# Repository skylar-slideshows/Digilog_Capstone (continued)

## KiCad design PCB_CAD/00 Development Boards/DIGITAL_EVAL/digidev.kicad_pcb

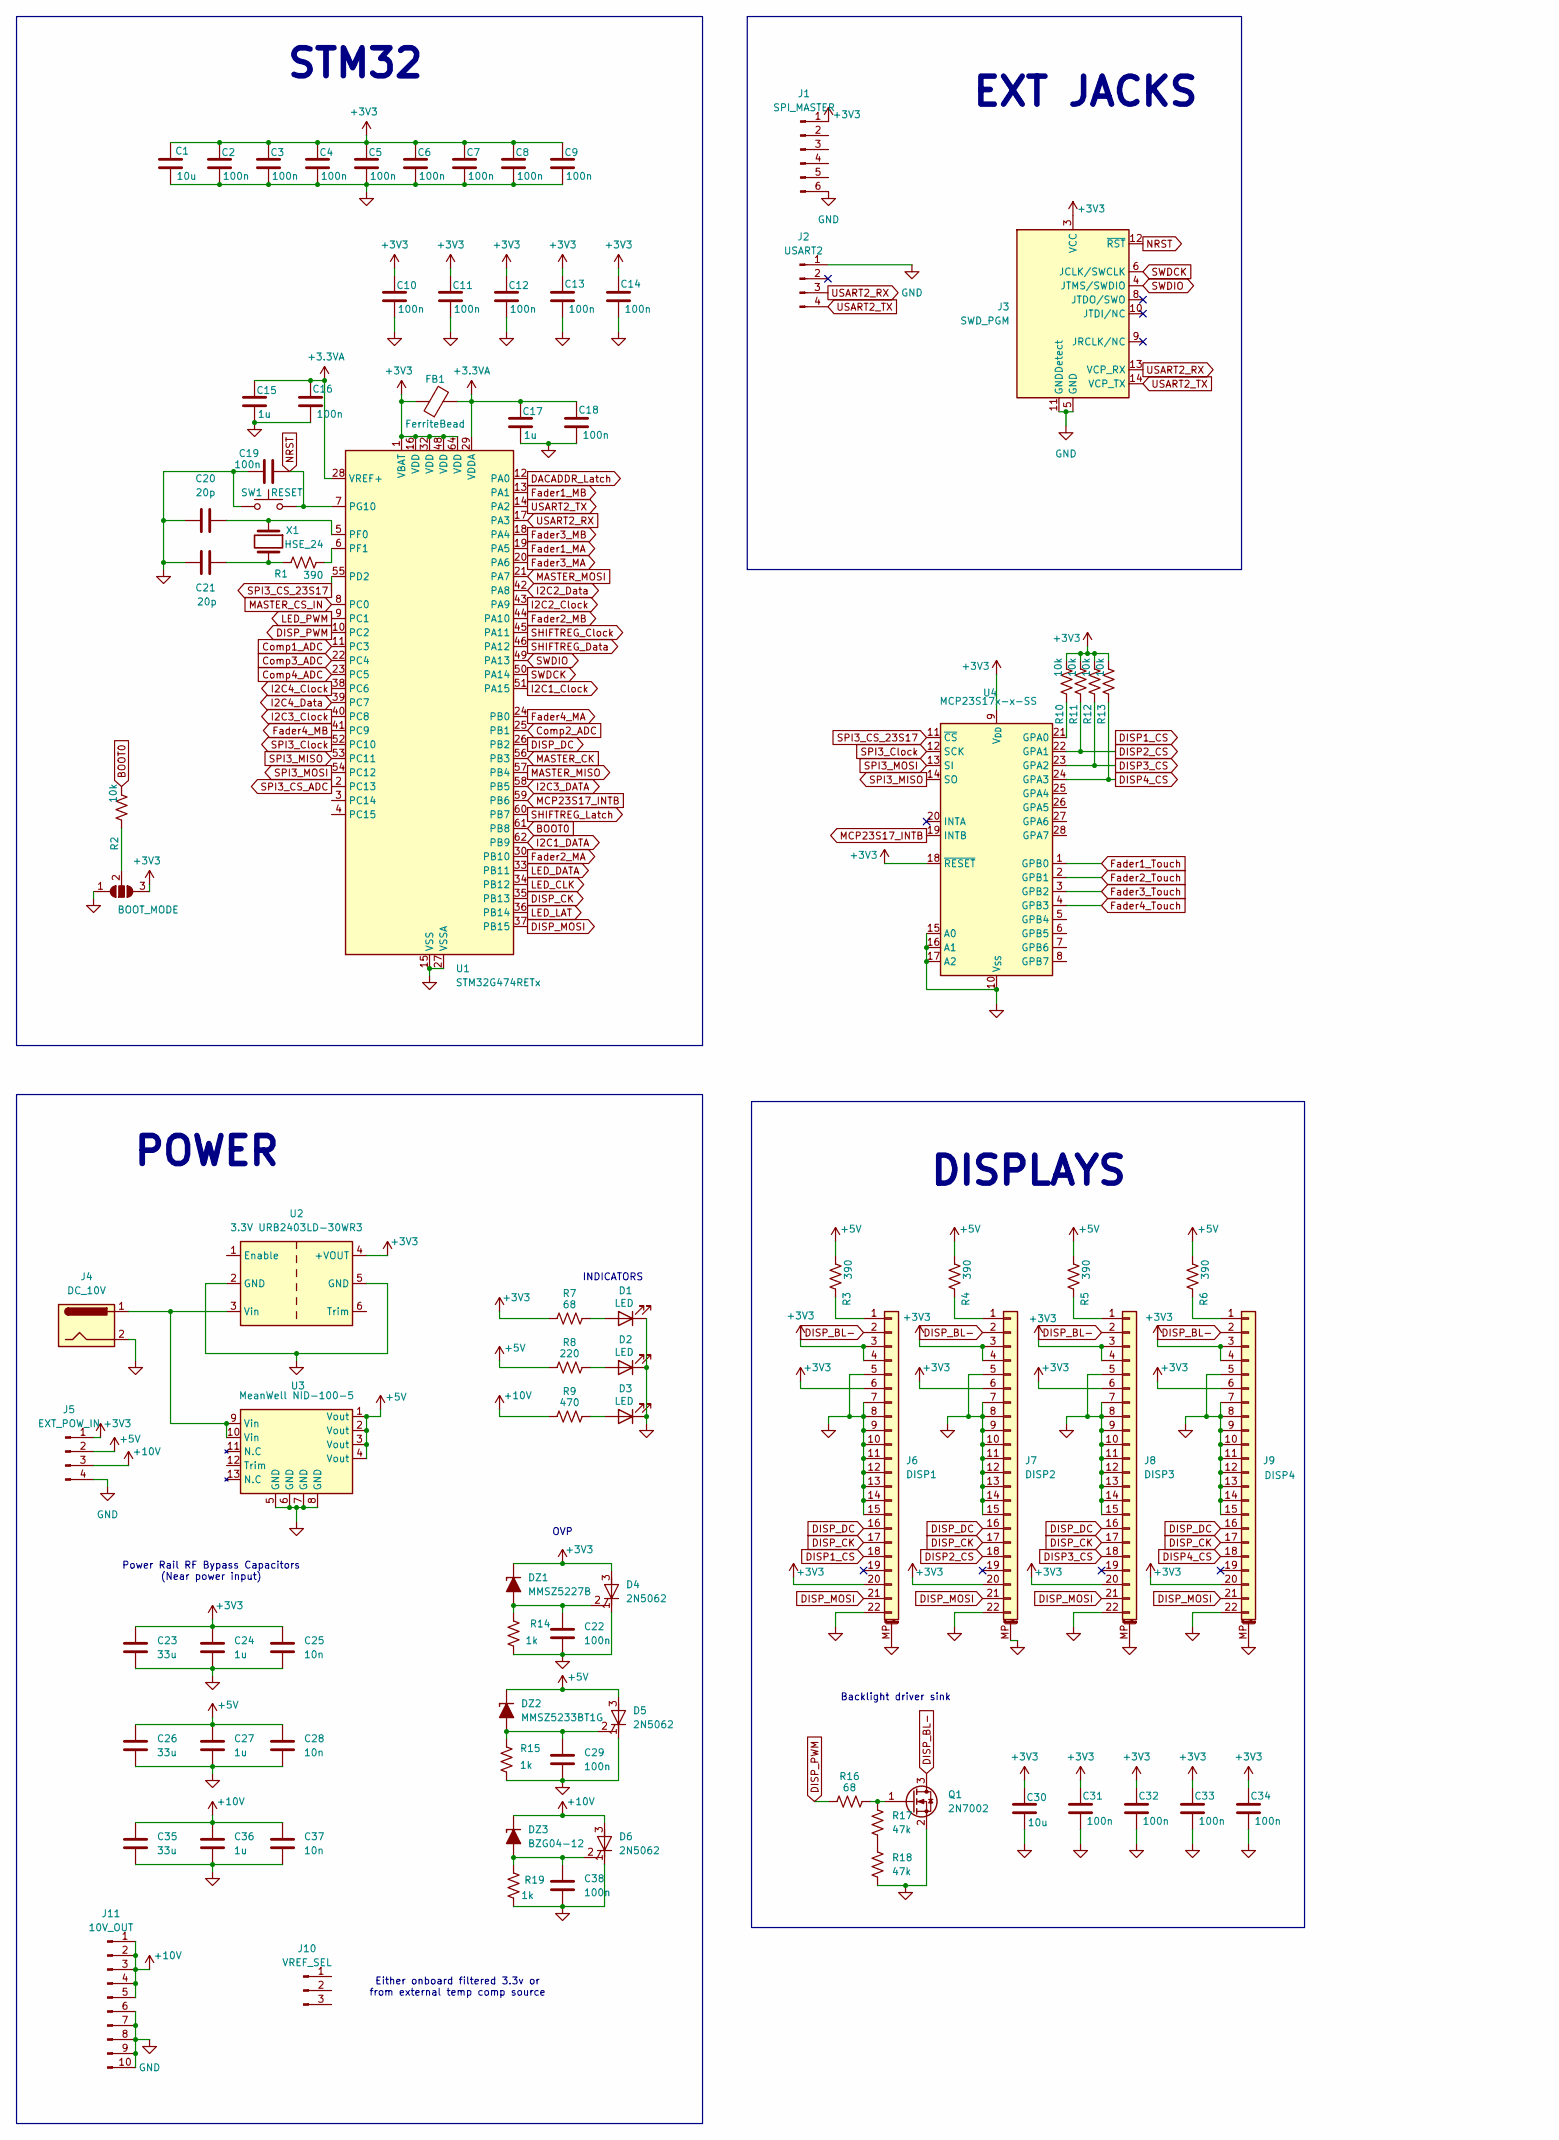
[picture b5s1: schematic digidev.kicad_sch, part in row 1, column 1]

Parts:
BOOT_MODE: SolderJumper_3_Open; SolderJumper-3_P2.0mm_Open_TrianglePad1.0x1.5mm
C1, C30: 10u; C_0805_2012Metric; LCSC C1713
C2, C3, C4, C5, C6, C7, C8, C9, C10, C11, C12, C13, C14, C16, C18, C19, C22, C29, C31, C32, C33, C34, C38: 100n; C_0603_1608Metric; LCSC C57112
C15, C17: 1u; C_0603_1608Metric; LCSC C57112
C20, C21: 20p; C_0603_1608Metric; LCSC C1648
C23, C26, C35: 33u; CP_Elec_6.3x5.4; LCSC C970684
C24, C27, C36: 1u; C_0603_1608Metric; LCSC C15849
C25, C28, C37: 10n; C_0603_1608Metric; LCSC C57112
D1, D2, D3: LED; LED_Rectangular_W3.9mm_H1.8mm
D4, D5, D6: 2N5062; TO-92
DZ1: MMSZ5227B; D_SOD-123; LCSC C707159
DZ2: MMSZ5233BT1G; D_SOD-123; LCSC C145506
DZ3: BZG04-12; D_DO-214AC_SMA; LCSC C5185905
FB1: FerriteBead; Ferrite_0603_1608Metric; LCSC C1002
J1: SPI_MASTER; PinHeader_1x06_P2.54mm_Vertical
J2: USART2; PinHeader_1x04_P2.54mm_Vertical
J3: SWD_PGM; FTSH-107-01-L-DV-K-TR; LCSC C5307809
J4: DC_10V; BarrelJack_Horizontal
J5: EXT_POW_IN; PinHeader_1x04_P2.54mm_Vertical
J6: DISP1; TE_2-1734839-2_1x22-1MP_P0.5mm_Horizontal; LCSC C22435644
J7: DISP2; TE_2-1734839-2_1x22-1MP_P0.5mm_Horizontal; LCSC C22435644
J8: DISP3; TE_2-1734839-2_1x22-1MP_P0.5mm_Horizontal; LCSC C22435644
J9: DISP4; TE_2-1734839-2_1x22-1MP_P0.5mm_Horizontal; LCSC C22435644
J10: VREF_SEL; PinHeader_1x03_P2.54mm_Vertical
J11: 10V_OUT; PinHeader_1x10_P2.54mm_Vertical
Q1: 2N7002; SOT-23; LCSC C85047
R1, R3, R4, R5, R6: 390; R_1206_3216Metric; LCSC C497314
R2, R10, R11, R12, R13: 10k; R_0603_1608Metric; LCSC C25804
R7, R16: 68; R_1206_3216Metric; LCSC C294793
R8: 220; R_1206_3216Metric; LCSC C25363
R9: 470; R_1206_3216Metric; LCSC C25383
R14, R15, R19: 1k; R_0603_1608Metric; LCSC C21190
R17, R18: 47k; R_0603_1608Metric; LCSC C25819
SW1: RESET; SW_Push_1P1T_NO_CK_KMR2; LCSC C72443
U1: STM32G474RETx; LQFP-64_10x10mm_P0.5mm; LCSC C521608
U2: 3.3V URB2403LD-30WR3; urb 50w dc-dc
U3: MeanWell NID-100-5; MeanWell NID100
U4: MCP23S17x-x-SS; SSOP-28_5.3x10.2mm_P0.65mm; LCSC C148009
X1: HSE_24; Crystal_SMD_HC49-SD; LCSC C117881

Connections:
+3.3VA: C15.1, C16.1, C17.1, C18.1, FB1.2, U1.28 (VREF+), U1.29 (VDDA); also elsewhere on the board
+3V3: BOOT_MODE.3 (B), C1.1, C2.1, C3.1, C4.1, C5.1, C6.1, C7.1, C8.1, C9.1, C10.1, C11.1, C12.1, C13.1, C14.1, C23.1, C24.1, C25.1, C30.1, C31.1, C32.1, C33.1, C34.1, D4.3 (A), DZ1.1 (K), FB1.1, J1.1, J3.3 (VCC), J5.1, J6.3, J6.4, J6.6, J6.20, J7.3, J7.4, J7.6, J7.20, J8.3, J8.4, J8.6, J8.20, J9.3, J9.4, J9.6, J9.20, R7.1, R10.1, R11.1, R12.1, R13.1, U1.1 (VBAT), U1.16 (VDD), U1.32 (VDD), U1.48 (VDD), U1.64 (VDD), U2.4 (+VOUT), U4.9 (V_{DD}), U4.18 (~RESET); also elsewhere on the board
+5V: C26.1, C27.1, C28.1, D5.3 (A), DZ2.1 (K), J5.2, R3.2, R4.2, R5.2, R6.2, R8.1, U3.1 (Vout), U3.2 (Vout), U3.3 (Vout), U3.4 (Vout)
+10V: C35.1, C36.1, C37.1, D6.3 (A), DZ3.1 (K), J5.3, J11.1, J11.2, J11.3, J11.4, J11.5, R9.1
BOOT0: R2.1, U1.61 (PB8)
Comp1_ADC: U1.11 (PC3)
Comp2_ADC: U1.25 (PB1)
Comp3_ADC: U1.22 (PC4)
Comp4_ADC: U1.23 (PC5)
DACADDR_Latch: U1.12 (PA0); also elsewhere on the board
DISP_BL-: J6.2, J7.2, J8.2, J9.2, Q1.3 (D)
DISP_CK: J6.17, J7.17, J8.17, J9.17, U1.35 (PB13)
DISP_DC: J6.16, J7.16, J8.16, J9.16, U1.26 (PB2)
DISP_MOSI: J6.21, J7.21, J8.21, J9.21, U1.37 (PB15)
DISP_PWM: R16.1, U1.10 (PC2)
Fader1_MA: U1.19 (PA5)
Fader1_MB: U1.13 (PA1)
Fader1_Touch: U4.1 (GPB0)
Fader2_MA: U1.30 (PB10)
Fader2_MB: U1.44 (PA10)
Fader2_Touch: U4.2 (GPB1)
Fader3_MA: U1.20 (PA6)
Fader3_MB: U1.18 (PA4)
Fader3_Touch: U4.3 (GPB2)
Fader4_MA: U1.24 (PB0)
Fader4_MB: U1.41 (PC9)
Fader4_Touch: U4.4 (GPB3)
GND: BOOT_MODE.1 (A), C1.2, C2.2, C3.2, C4.2, C5.2, C6.2, C7.2, C8.2, C9.2, C10.2, C11.2, C12.2, C13.2, C14.2, C15.2, C16.2, C17.2, C18.2, C19.1, C20.2, C21.1, C22.2, C23.2, C24.2, C25.2, C26.2, C27.2, C28.2, C29.2, C30.2, C31.2, C32.2, C33.2, C34.2, C35.2, C36.2, C37.2, C38.2, D1.1 (K), D2.1 (K), D3.1 (K), D4.1 (K), D5.1 (K), D6.1 (K), J1.6, J2.1, J3.5 (GND), J3.7 (GND), J3.11 (GNDDetect), J4.2, J5.4, J6.5, J6.7, J6.8, J6.9, J6.10, J6.11, J6.12, J6.13, J6.14, J6.15, J6.22, J6.MP (MountPin), J7.5, J7.7, J7.8, J7.9, J7.10, J7.11, J7.12, J7.13, J7.14, J7.15, J7.22, J7.MP (MountPin), J8.5, J8.7, J8.8, J8.9, J8.10, J8.11, J8.12, J8.13, J8.14, J8.15, J8.22, J8.MP (MountPin), J9.5, J9.7, J9.8, J9.9, J9.10, J9.11, J9.12, J9.13, J9.14, J9.15, J9.22, J9.MP (MountPin), J11.6, J11.7, J11.8, J11.9, J11.10, Q1.2 (S), R14.1, R15.1, R18.2, R19.2, SW1.1, U1.15 (VSS), U1.27 (VSSA), U1.31 (VSS), U1.47 (VSS), U1.63 (VSS), U2.2 (GND), U2.5 (GND), U3.5 (GND), U3.6 (GND), U3.7 (GND), U3.8 (GND), U4.10 (V_{SS}), U4.15 (A0), U4.16 (A1), U4.17 (A2); also elsewhere on the board
I2C1_Clock: U1.51 (PA15); also elsewhere on the board
I2C1_DATA: U1.62 (PB9); also elsewhere on the board
I2C2_Clock: U1.43 (PA9); also elsewhere on the board
I2C2_Data: U1.42 (PA8); also elsewhere on the board
I2C3_Clock: U1.40 (PC8); also elsewhere on the board
I2C3_DATA: U1.58 (PB5); also elsewhere on the board
I2C4_Clock: U1.38 (PC6); also elsewhere on the board
I2C4_Data: U1.39 (PC7); also elsewhere on the board
LED_CLK: U1.34 (PB12)
LED_DATA: U1.33 (PB11)
LED_LAT: U1.36 (PB14)
LED_PWM: U1.9 (PC1)
MASTER_CK: U1.56 (PB3)
MASTER_CS_IN: U1.8 (PC0)
MASTER_MISO: U1.57 (PB4)
MASTER_MOSI: U1.21 (PA7)
MCP23S17_INTB: U1.59 (PB6), U4.19 (INTB)
NRST: C19.2, J3.12 (~RST), SW1.2, U1.7 (PG10)
unnamed 66: BOOT_MODE.2 (C), R2.2; also elsewhere on the board
unnamed: C21.2, R1.1, X1.2
unnamed: D1.2 (A), R7.2
unnamed: D2.2 (A), R8.2
unnamed: D3.2 (A), R9.2
unnamed: C22.1, D4.2 (G), DZ1.2 (A), R14.2
unnamed: C29.1, D5.2 (G), DZ2.2 (A), R15.2
unnamed: C38.1, D6.2 (G), DZ3.2 (A), R19.1
unnamed: J6.1, R3.1
unnamed: J7.1, R4.1
unnamed: J8.1, R5.1
unnamed: J9.1, R6.1
unnamed: Q1.1 (G), R16.2, R17.1
unnamed: R17.2, R18.1
unnamed: C20.1, U1.5 (PF0), X1.1
unnamed: R1.2, U1.6 (PF1)
unnamed: J4.1, U2.3 (Vin), U3.9 (Vin), U3.10 (Vin)
SHIFTREG_Clock: U1.45 (PA11); also elsewhere on the board
SHIFTREG_Data: U1.46 (PA12); also elsewhere on the board
SHIFTREG_Latch: U1.60 (PB7); also elsewhere on the board
SPI3_CS_23S17: U1.55 (PD2), U4.11 (~CS)
SPI3_CS_ADC: U1.2 (PC13)
SPI3_Clock: U1.52 (PC10), U4.12 (SCK)
SPI3_MISO: U1.53 (PC11), U4.14 (SO)
SPI3_MOSI: U1.54 (PC12), U4.13 (SI)
SWDCK: J3.6 (JCLK/SWCLK), U1.50 (PA14)
SWDIO: J3.4 (JTMS/SWDIO), U1.49 (PA13)
USART2_RX: J2.3, J3.13 (VCP_RX), U1.17 (PA3)
USART2_TX: J2.4, J3.14 (VCP_TX), U1.14 (PA2)

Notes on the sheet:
Either onboard filtered 3.3v or from external temp comp source
STM32
INDICATORS
EXT JACKS
OVP
DISPLAYS
Backlight driver sink
Power Rail RF Bypass Capacitors (Near power input)
POWER

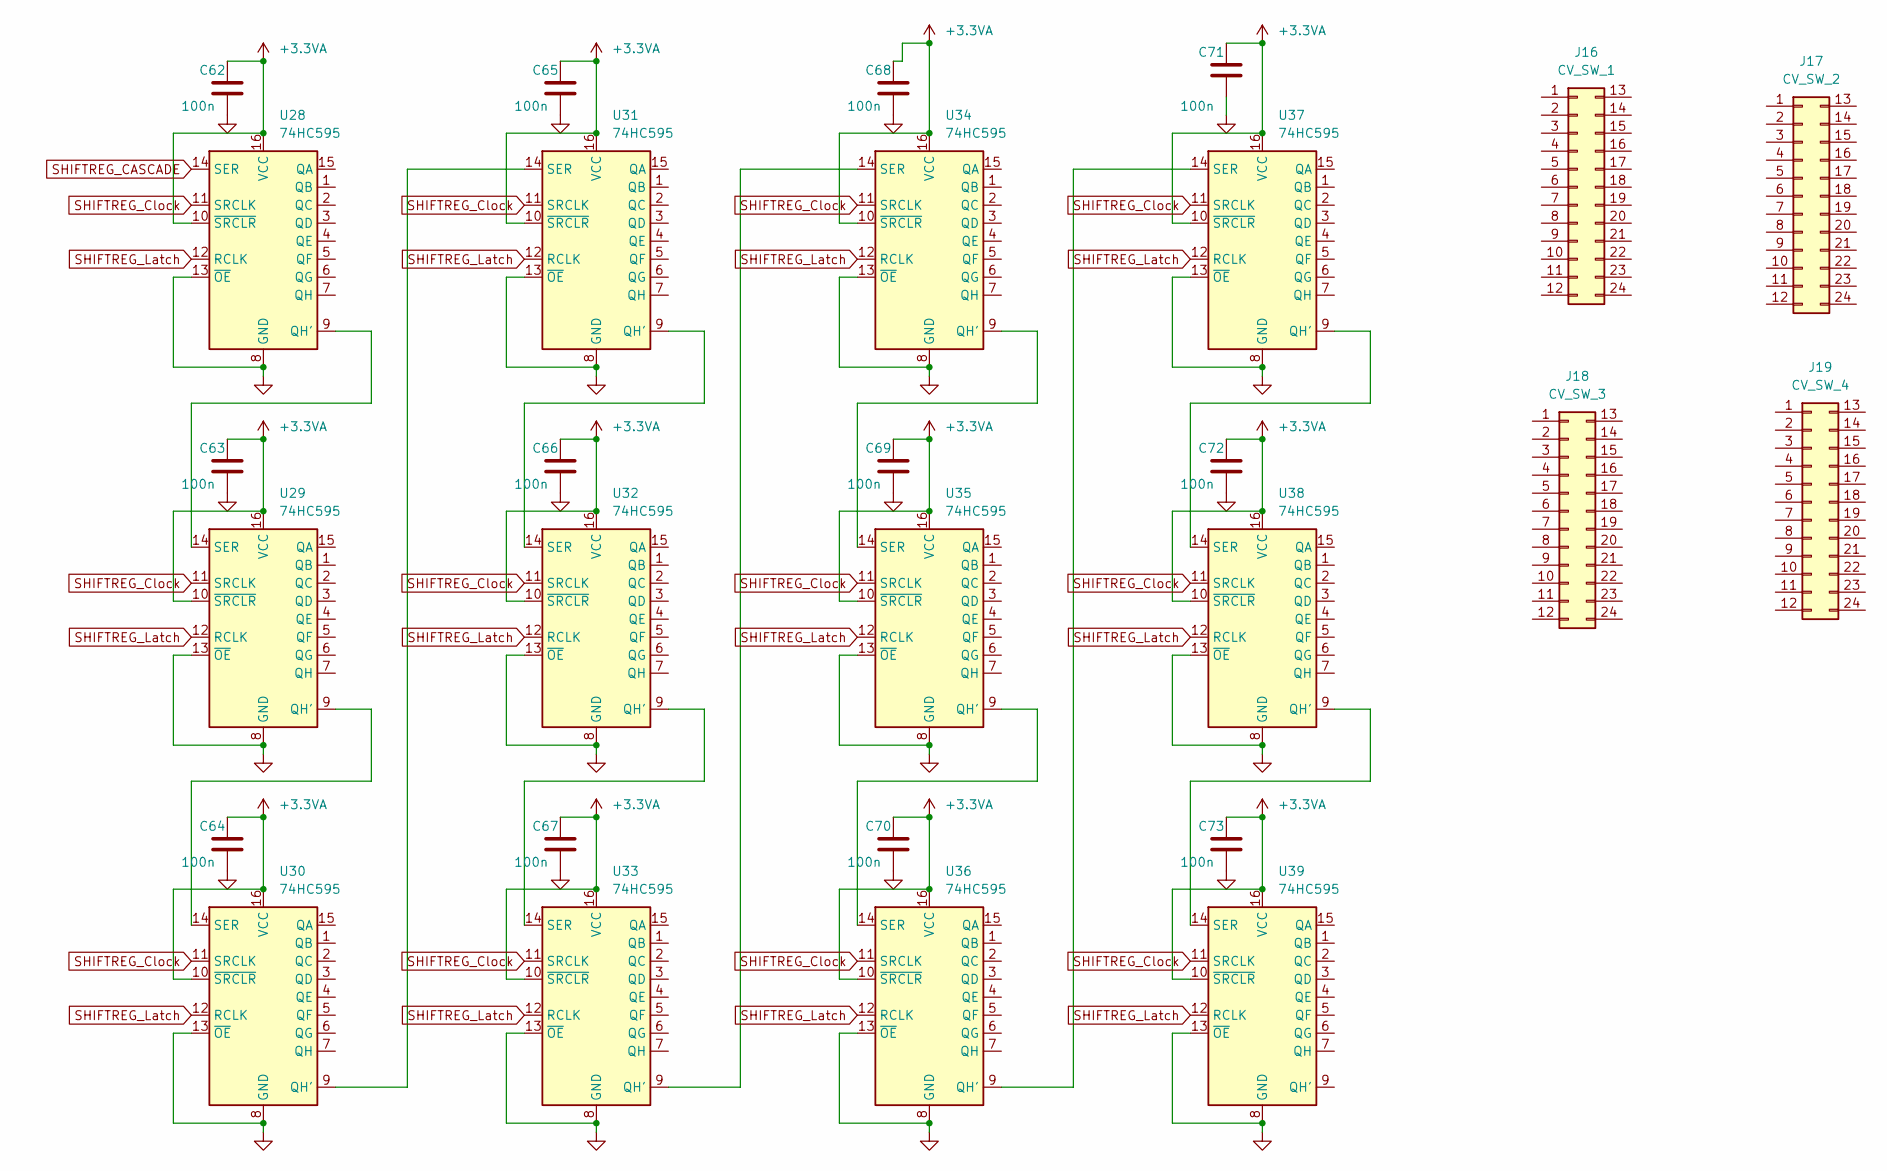
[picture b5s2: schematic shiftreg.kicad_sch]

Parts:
C62, C63, C64, C65, C66, C67, C68, C69, C70, C71, C72, C73: 100n; C_0402_1005Metric; LCSC C1525
J16: CV_SW_1; PinHeader_2x12_P2.54mm_Vertical
J17: CV_SW_2; PinHeader_2x12_P2.54mm_Vertical
J18: CV_SW_3; PinHeader_2x12_P2.54mm_Vertical
J19: CV_SW_4; PinHeader_2x12_P2.54mm_Vertical
U28, U29, U30, U31, U32, U33, U34, U35, U36, U37, U38, U39: 74HC595; TSSOP-16_4.4x5mm_P0.65mm; LCSC C5948

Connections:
+3.3VA: C62.1, C63.1, C64.1, C65.1, C66.1, C67.1, C68.1, C69.1, C70.1, C71.1, C72.1, C73.1, U28.10 (~SRCLR), U28.16 (VCC), U29.10 (~SRCLR), U29.16 (VCC), U30.10 (~SRCLR), U30.16 (VCC), U31.10 (~SRCLR), U31.16 (VCC), U32.10 (~SRCLR), U32.16 (VCC), U33.10 (~SRCLR), U33.16 (VCC), U34.10 (~SRCLR), U34.16 (VCC), U35.10 (~SRCLR), U35.16 (VCC), U36.10 (~SRCLR), U36.16 (VCC), U37.10 (~SRCLR), U37.16 (VCC), U38.10 (~SRCLR), U38.16 (VCC), U39.10 (~SRCLR), U39.16 (VCC); also elsewhere on the board
GND: C62.2, C63.2, C64.2, C65.2, C66.2, C67.2, C68.2, C69.2, C70.2, C71.2, C72.2, C73.2, U28.8 (GND), U28.13 (~OE), U29.8 (GND), U29.13 (~OE), U30.8 (GND), U30.13 (~OE), U31.8 (GND), U31.13 (~OE), U32.8 (GND), U32.13 (~OE), U33.8 (GND), U33.13 (~OE), U34.8 (GND), U34.13 (~OE), U35.8 (GND), U35.13 (~OE), U36.8 (GND), U36.13 (~OE), U37.8 (GND), U37.13 (~OE), U38.8 (GND), U38.13 (~OE), U39.8 (GND), U39.13 (~OE); also elsewhere on the board
unnamed: U28.9 (QH'), U29.14 (SER)
unnamed: U29.9 (QH'), U30.14 (SER)
unnamed: U30.9 (QH'), U31.14 (SER)
unnamed: U31.9 (QH'), U32.14 (SER)
unnamed: U32.9 (QH'), U33.14 (SER)
unnamed: U33.9 (QH'), U34.14 (SER)
unnamed: U34.9 (QH'), U35.14 (SER)
unnamed: U35.9 (QH'), U36.14 (SER)
unnamed: U36.9 (QH'), U37.14 (SER)
unnamed: U37.9 (QH'), U38.14 (SER)
unnamed: U38.9 (QH'), U39.14 (SER)
SHIFTREG_CASCADE: U28.14 (SER); also elsewhere on the board
SHIFTREG_Clock: U28.11 (SRCLK), U29.11 (SRCLK), U30.11 (SRCLK), U31.11 (SRCLK), U32.11 (SRCLK), U33.11 (SRCLK), U34.11 (SRCLK), U35.11 (SRCLK), U36.11 (SRCLK), U37.11 (SRCLK), U38.11 (SRCLK), U39.11 (SRCLK); also elsewhere on the board
SHIFTREG_Latch: U28.12 (RCLK), U29.12 (RCLK), U30.12 (RCLK), U31.12 (RCLK), U32.12 (RCLK), U33.12 (RCLK), U34.12 (RCLK), U35.12 (RCLK), U36.12 (RCLK), U37.12 (RCLK), U38.12 (RCLK), U39.12 (RCLK); also elsewhere on the board

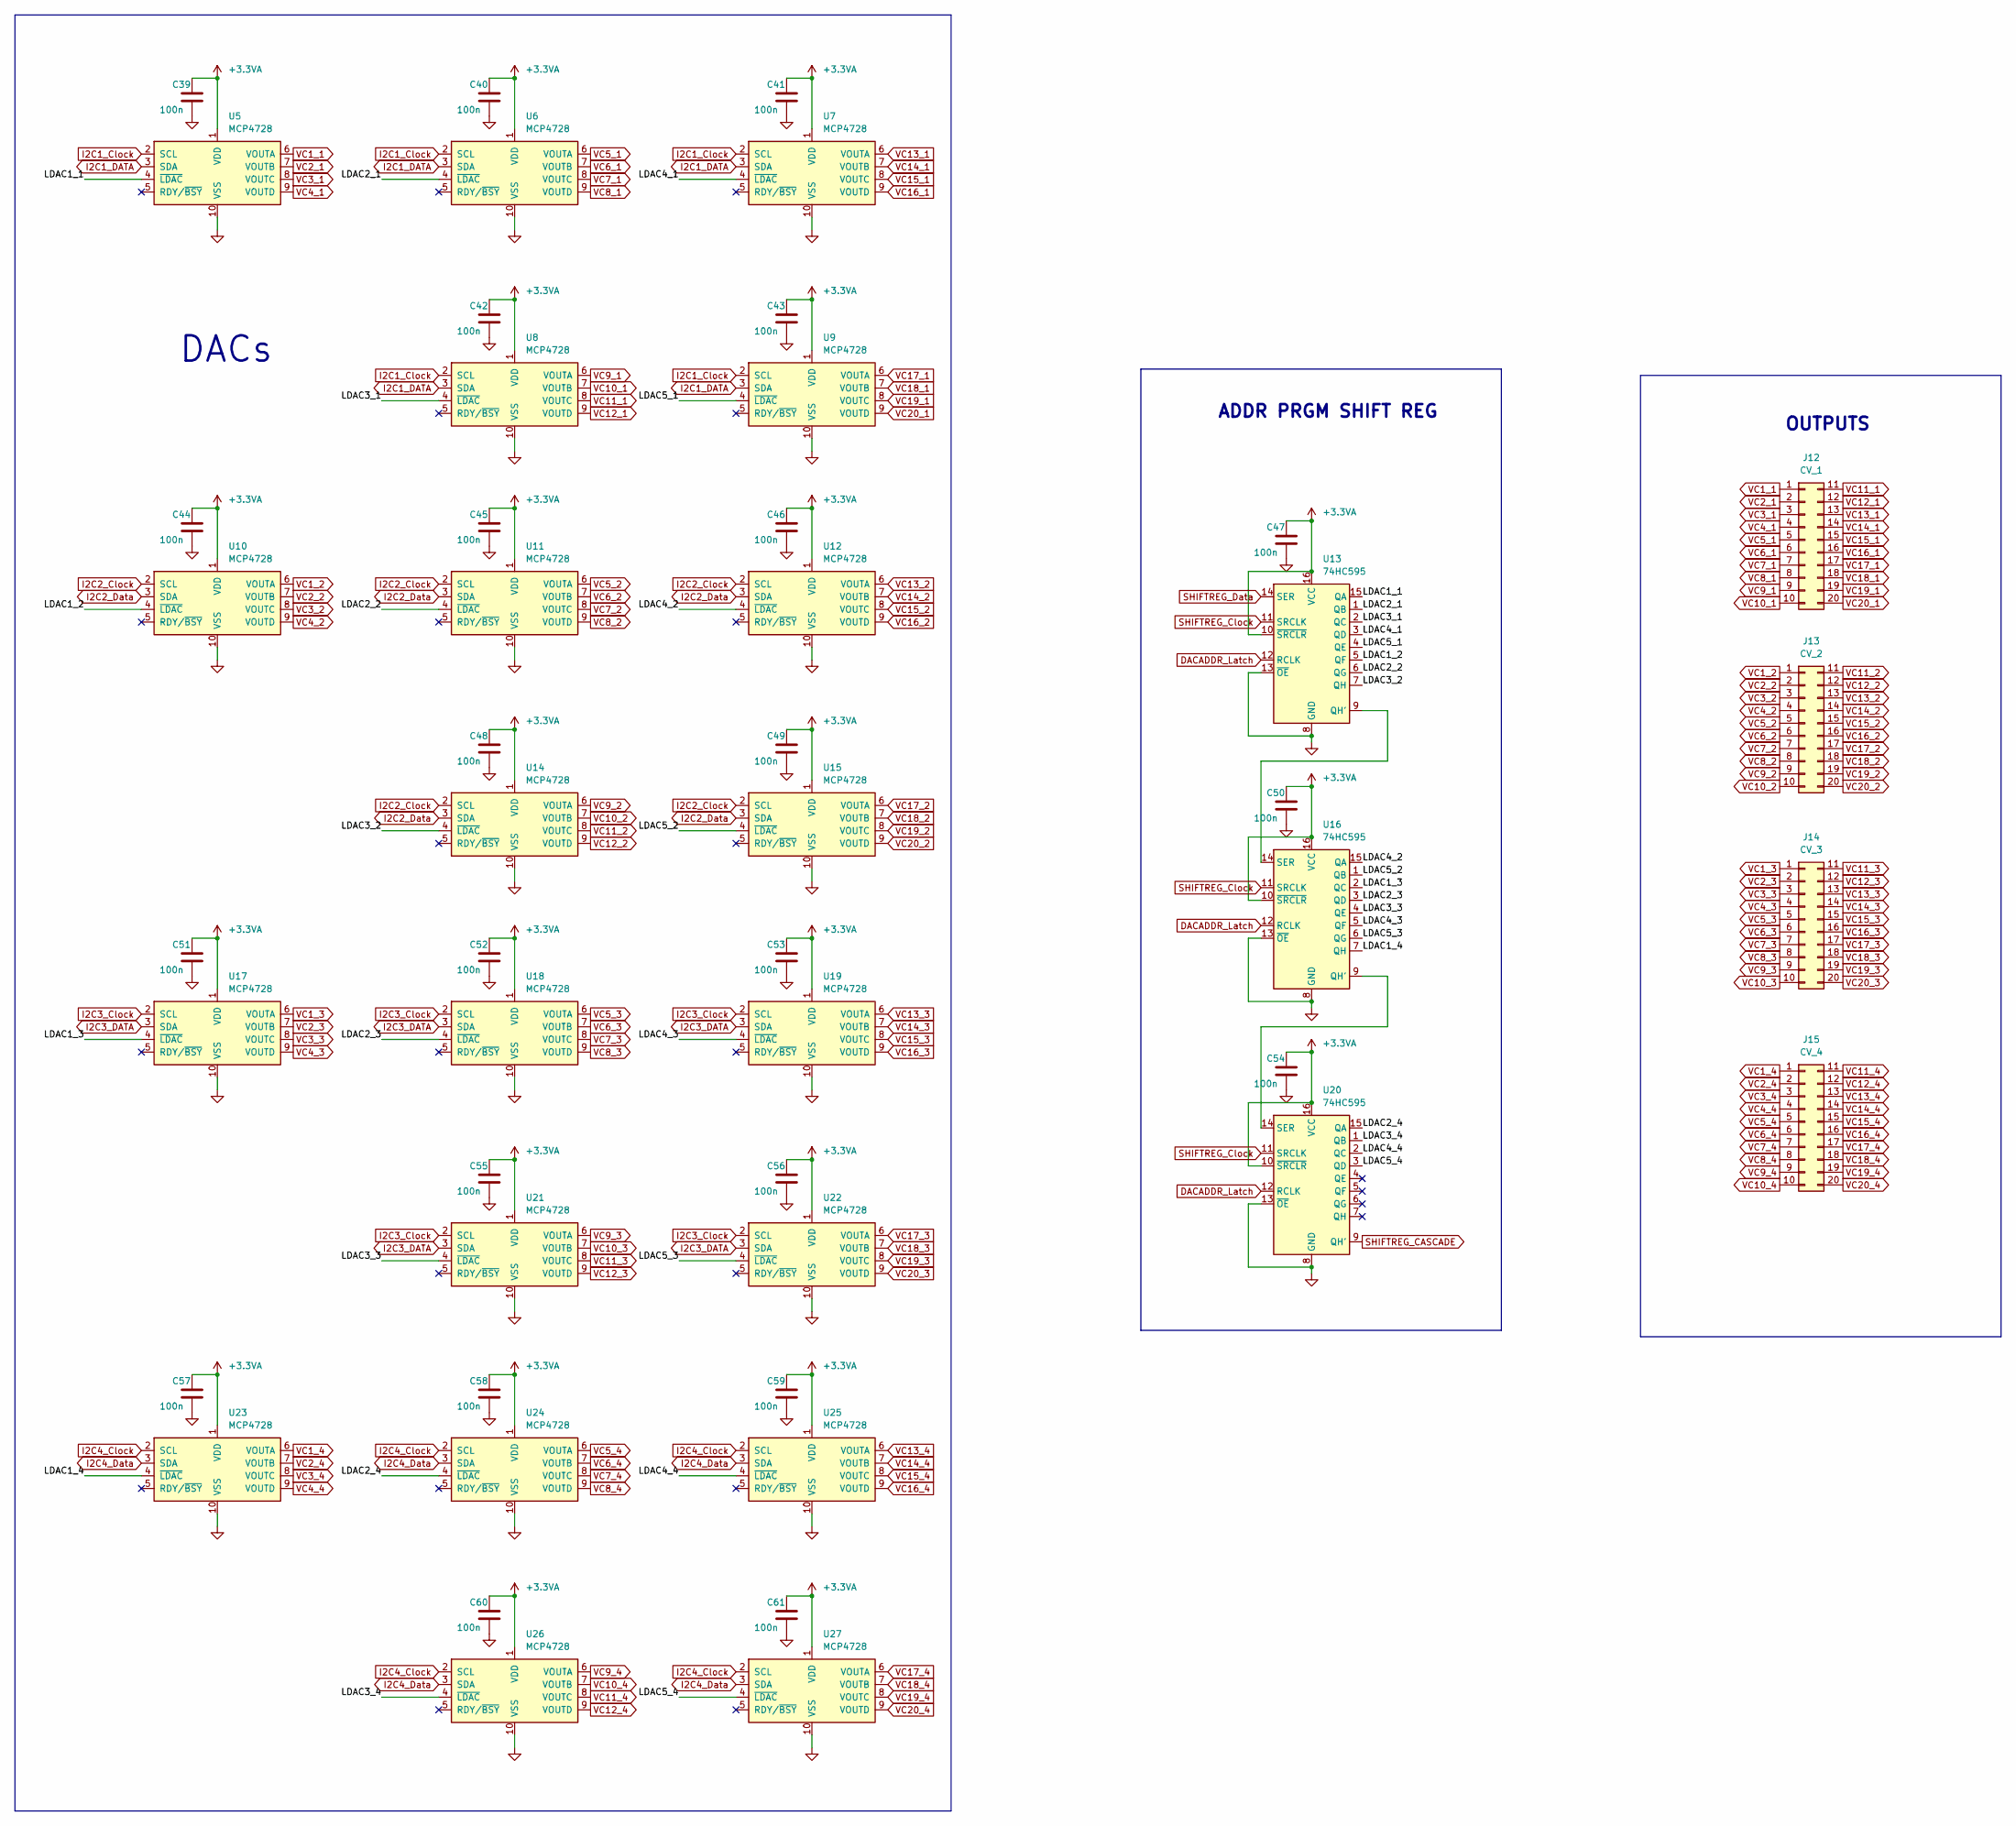
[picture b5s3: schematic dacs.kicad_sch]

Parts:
C39, C40, C41, C42, C43, C44, C45, C46, C47, C48, C49, C50, C51, C52, C53, C54, C55, C56, C57, C58, C59, C60, C61: 100n; C_0402_1005Metric; LCSC C1525
J12: CV_1; PinHeader_2x10_P2.54mm_Vertical
J13: CV_2; PinHeader_2x10_P2.54mm_Vertical
J14: CV_3; PinHeader_2x10_P2.54mm_Vertical
J15: CV_4; PinHeader_2x10_P2.54mm_Vertical
U5, U6, U7, U8, U9, U10, U11, U12, U14, U15, U17, U18, U19, U21, U22, U23, U24, U25, U26, U27: MCP4728; MSOP-10_3x3mm_P0.5mm; LCSC C478093
U13, U16, U20: 74HC595; TSSOP-16_4.4x5mm_P0.65mm; LCSC C5948

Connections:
+3.3VA: C39.1, C40.1, C41.1, C42.1, C43.1, C44.1, C45.1, C46.1, C47.1, C48.1, C49.1, C50.1, C51.1, C52.1, C53.1, C54.1, C55.1, C56.1, C57.1, C58.1, C59.1, C60.1, C61.1, U5.1 (VDD), U6.1 (VDD), U7.1 (VDD), U8.1 (VDD), U9.1 (VDD), U10.1 (VDD), U11.1 (VDD), U12.1 (VDD), U13.10 (~SRCLR), U13.16 (VCC), U14.1 (VDD), U15.1 (VDD), U16.10 (~SRCLR), U16.16 (VCC), U17.1 (VDD), U18.1 (VDD), U19.1 (VDD), U20.10 (~SRCLR), U20.16 (VCC), U21.1 (VDD), U22.1 (VDD), U23.1 (VDD), U24.1 (VDD), U25.1 (VDD), U26.1 (VDD), U27.1 (VDD); also elsewhere on the board
/DACs/LDAC1_1: U5.4 (~LDAC), U13.15 (QA)
/DACs/LDAC1_2: U10.4 (~LDAC), U13.5 (QF)
/DACs/LDAC1_3: U16.2 (QC), U17.4 (~LDAC)
/DACs/LDAC1_4: U16.7 (QH), U23.4 (~LDAC)
/DACs/LDAC2_1: U6.4 (~LDAC), U13.1 (QB)
/DACs/LDAC2_2: U11.4 (~LDAC), U13.6 (QG)
/DACs/LDAC2_3: U16.3 (QD), U18.4 (~LDAC)
/DACs/LDAC2_4: U20.15 (QA), U24.4 (~LDAC)
/DACs/LDAC3_1: U8.4 (~LDAC), U13.2 (QC)
/DACs/LDAC3_2: U13.7 (QH), U14.4 (~LDAC)
/DACs/LDAC3_3: U16.4 (QE), U21.4 (~LDAC)
/DACs/LDAC3_4: U20.1 (QB), U26.4 (~LDAC)
/DACs/LDAC4_1: U7.4 (~LDAC), U13.3 (QD)
/DACs/LDAC4_2: U12.4 (~LDAC), U16.15 (QA)
/DACs/LDAC4_3: U16.5 (QF), U19.4 (~LDAC)
/DACs/LDAC4_4: U20.2 (QC), U25.4 (~LDAC)
/DACs/LDAC5_1: U9.4 (~LDAC), U13.4 (QE)
/DACs/LDAC5_2: U15.4 (~LDAC), U16.1 (QB)
/DACs/LDAC5_3: U16.6 (QG), U22.4 (~LDAC)
/DACs/LDAC5_4: U20.3 (QD), U27.4 (~LDAC)
DACADDR_Latch: U13.12 (RCLK), U16.12 (RCLK), U20.12 (RCLK); also elsewhere on the board
GND: C39.2, C40.2, C41.2, C42.2, C43.2, C44.2, C45.2, C46.2, C47.2, C48.2, C49.2, C50.2, C51.2, C52.2, C53.2, C54.2, C55.2, C56.2, C57.2, C58.2, C59.2, C60.2, C61.2, U5.10 (VSS), U6.10 (VSS), U7.10 (VSS), U8.10 (VSS), U9.10 (VSS), U10.10 (VSS), U11.10 (VSS), U12.10 (VSS), U13.8 (GND), U13.13 (~OE), U14.10 (VSS), U15.10 (VSS), U16.8 (GND), U16.13 (~OE), U17.10 (VSS), U18.10 (VSS), U19.10 (VSS), U20.8 (GND), U20.13 (~OE), U21.10 (VSS), U22.10 (VSS), U23.10 (VSS), U24.10 (VSS), U25.10 (VSS), U26.10 (VSS), U27.10 (VSS); also elsewhere on the board
I2C1_Clock: U5.2 (SCL), U6.2 (SCL), U7.2 (SCL), U8.2 (SCL), U9.2 (SCL); also elsewhere on the board
I2C1_DATA: U5.3 (SDA), U6.3 (SDA), U7.3 (SDA), U8.3 (SDA), U9.3 (SDA); also elsewhere on the board
I2C2_Clock: U10.2 (SCL), U11.2 (SCL), U12.2 (SCL), U14.2 (SCL), U15.2 (SCL); also elsewhere on the board
I2C2_Data: U10.3 (SDA), U11.3 (SDA), U12.3 (SDA), U14.3 (SDA), U15.3 (SDA); also elsewhere on the board
I2C3_Clock: U17.2 (SCL), U18.2 (SCL), U19.2 (SCL), U21.2 (SCL), U22.2 (SCL); also elsewhere on the board
I2C3_DATA: U17.3 (SDA), U18.3 (SDA), U19.3 (SDA), U21.3 (SDA), U22.3 (SDA); also elsewhere on the board
I2C4_Clock: U23.2 (SCL), U24.2 (SCL), U25.2 (SCL), U26.2 (SCL), U27.2 (SCL); also elsewhere on the board
I2C4_Data: U23.3 (SDA), U24.3 (SDA), U25.3 (SDA), U26.3 (SDA), U27.3 (SDA); also elsewhere on the board
unnamed: U13.9 (QH'), U16.14 (SER)
unnamed: U16.9 (QH'), U20.14 (SER)
SHIFTREG_CASCADE: U20.9 (QH'); also elsewhere on the board
SHIFTREG_Clock: U13.11 (SRCLK), U16.11 (SRCLK), U20.11 (SRCLK); also elsewhere on the board
SHIFTREG_Data: U13.14 (SER); also elsewhere on the board
VC1_1: J12.1, U5.6 (VOUTA)
VC1_2: J13.1, U10.6 (VOUTA)
VC1_3: J14.1, U17.6 (VOUTA)
VC1_4: J15.1, U23.6 (VOUTA)
VC2_1: J12.2, U5.7 (VOUTB)
VC2_2: J13.2, U10.7 (VOUTB)
VC2_3: J14.2, U17.7 (VOUTB)
VC2_4: J15.2, U23.7 (VOUTB)
VC3_1: J12.3, U5.8 (VOUTC)
VC3_2: J13.3, U10.8 (VOUTC)
VC3_3: J14.3, U17.8 (VOUTC)
VC3_4: J15.3, U23.8 (VOUTC)
VC4_1: J12.4, U5.9 (VOUTD)
VC4_2: J13.4, U10.9 (VOUTD)
VC4_3: J14.4, U17.9 (VOUTD)
VC4_4: J15.4, U23.9 (VOUTD)
VC5_1: J12.5, U6.6 (VOUTA)
VC5_2: J13.5, U11.6 (VOUTA)
VC5_3: J14.5, U18.6 (VOUTA)
VC5_4: J15.5, U24.6 (VOUTA)
VC6_1: J12.6, U6.7 (VOUTB)
VC6_2: J13.6, U11.7 (VOUTB)
VC6_3: J14.6, U18.7 (VOUTB)
VC6_4: J15.6, U24.7 (VOUTB)
VC7_1: J12.7, U6.8 (VOUTC)
VC7_2: J13.7, U11.8 (VOUTC)
VC7_3: J14.7, U18.8 (VOUTC)
VC7_4: J15.7, U24.8 (VOUTC)
VC8_1: J12.8, U6.9 (VOUTD)
VC8_2: J13.8, U11.9 (VOUTD)
VC8_3: J14.8, U18.9 (VOUTD)
VC8_4: J15.8, U24.9 (VOUTD)
VC9_1: J12.9, U8.6 (VOUTA)
VC9_2: J13.9, U14.6 (VOUTA)
VC9_3: J14.9, U21.6 (VOUTA)
VC9_4: J15.9, U26.6 (VOUTA)
VC10_1: J12.10, U8.7 (VOUTB)
VC10_2: J13.10, U14.7 (VOUTB)
VC10_3: J14.10, U21.7 (VOUTB)
VC10_4: J15.10, U26.7 (VOUTB)
VC11_1: J12.11, U8.8 (VOUTC)
VC11_2: J13.11, U14.8 (VOUTC)
VC11_3: J14.11, U21.8 (VOUTC)
VC11_4: J15.11, U26.8 (VOUTC)
VC12_1: J12.12, U8.9 (VOUTD)
VC12_2: J13.12, U14.9 (VOUTD)
VC12_3: J14.12, U21.9 (VOUTD)
VC12_4: J15.12, U26.9 (VOUTD)
VC13_1: J12.13, U7.6 (VOUTA)
VC13_2: J13.13, U12.6 (VOUTA)
VC13_3: J14.13, U19.6 (VOUTA)
VC13_4: J15.13, U25.6 (VOUTA)
VC14_1: J12.14, U7.7 (VOUTB)
VC14_2: J13.14, U12.7 (VOUTB)
VC14_3: J14.14, U19.7 (VOUTB)
VC14_4: J15.14, U25.7 (VOUTB)
VC15_1: J12.15, U7.8 (VOUTC)
VC15_2: J13.15, U12.8 (VOUTC)
VC15_3: J14.15, U19.8 (VOUTC)
VC15_4: J15.15, U25.8 (VOUTC)
VC16_1: J12.16, U7.9 (VOUTD)
VC16_2: J13.16, U12.9 (VOUTD)
VC16_3: J14.16, U19.9 (VOUTD)
VC16_4: J15.16, U25.9 (VOUTD)
VC17_1: J12.17, U9.6 (VOUTA)
VC17_2: J13.17, U15.6 (VOUTA)
VC17_3: J14.17, U22.6 (VOUTA)
VC17_4: J15.17, U27.6 (VOUTA)
VC18_1: J12.18, U9.7 (VOUTB)
VC18_2: J13.18, U15.7 (VOUTB)
VC18_3: J14.18, U22.7 (VOUTB)
VC18_4: J15.18, U27.7 (VOUTB)
VC19_1: J12.19, U9.8 (VOUTC)
VC19_2: J13.19, U15.8 (VOUTC)
VC19_3: J14.19, U22.8 (VOUTC)
VC19_4: J15.19, U27.8 (VOUTC)
VC20_1: J12.20, U9.9 (VOUTD)
VC20_2: J13.20, U15.9 (VOUTD)
VC20_3: J14.20, U22.9 (VOUTD)
VC20_4: J15.20, U27.9 (VOUTD)

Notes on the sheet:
DACs
OUTPUTS
ADDR PRGM SHIFT REG

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
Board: 2 copper layers, 164 parts (0 on the bottom side), 168 nets, no tracks yet.

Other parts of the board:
BOOT_MODE1: SolderJumper_3_Open; SolderJumper-3_P2.0mm_Open_TrianglePad1.0x1.5mm

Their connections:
+3V3: BOOT_MODE1.3 (B); also elsewhere on the board
GND: BOOT_MODE1.1 (A); also elsewhere on the board
unnamed 66: BOOT_MODE1.2 (C); also elsewhere on the board
